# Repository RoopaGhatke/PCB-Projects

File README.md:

This repository showcases a collection of PCB design projects created using Altium Designer and KiCad. 
Each project involves complete development from schematic design to PCB layout and 3D model visualization.
These designs were developed from scratch as part of my self-learning journey, following well-structured tutorials to understand and apply industry-standard design principles. 
These projects not only helped me gain hands-on experience with PCB design tools and workflows, but also deepened my understanding of hardware design concepts, electrical best practices and design-for-manufacturing (DFM) techniques.

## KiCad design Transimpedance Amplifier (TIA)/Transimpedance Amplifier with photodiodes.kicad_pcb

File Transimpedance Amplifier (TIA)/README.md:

Transimpedance Amplifier with Photodiodes – Circuit Design Lab

This repository documents the week-long Circuit Design Laboratory course project where I designed, simulated, fabricated, and tested a Transimpedance Amplifier (TIA) using photodiodes. 
The work involved both hardware and simulation aspects using KiCad and PCB prototyping tools.

Project Overview
The goal was to design a transimpedance amplifier circuit to convert photocurrent from a photodiode into a measurable voltage. 
The project was carried out step by step — from schematic design to simulation, PCB layout, fabrication, soldering and final testing.

Tools Used
KiCad for schematic design, simulation (DC, AC, and transient), and PCB layout
PCB etching tools for single and double-layer board fabrication
Basic electronics lab tools for assembly and testing (multimeter, soldering iron, etc.)

Key Design Highlights

1. Circuit Type: Transimpedance amplifier using photodiodes
2. Simulation:
   DC Analysis: Verified operating point and biasing
   AC Analysis: Observed frequency response and gain-bandwidth
   Transient Analysis: Verified dynamic behavior to input signal changes
3. PCB Layouts:
   Designed both single-layer and double-layer PCBs
   Included placement of photodiodes, op-amp, feedback resistor and capacitor, power supply pins, and headers

Fabrication & Testing Insights

1. Double-Layer PCB Issues:
   Over-etching due to prolonged etching bath exposure
   Heat damage during soldering caused pin header sinking
   Via placement too close to traces led to short circuits

2. Single-Layer PCB Success:
   Proper etching and trace definition
   Stable soldering and component mounting
   Functional test successful with clean output response

Visual Documentation
Images are available in the /images directory:
Double-layer board (defective): shorted vias, over-etching
Single-layer board (working): clean layout, successful testing

Learnings
Hands-on experience with full PCB design cycle
Impact of layout decisions on board performance
Importance of thermal control during soldering
Troubleshooting real-world fabrication errors
Value of simulation in verifying design before manufacturing

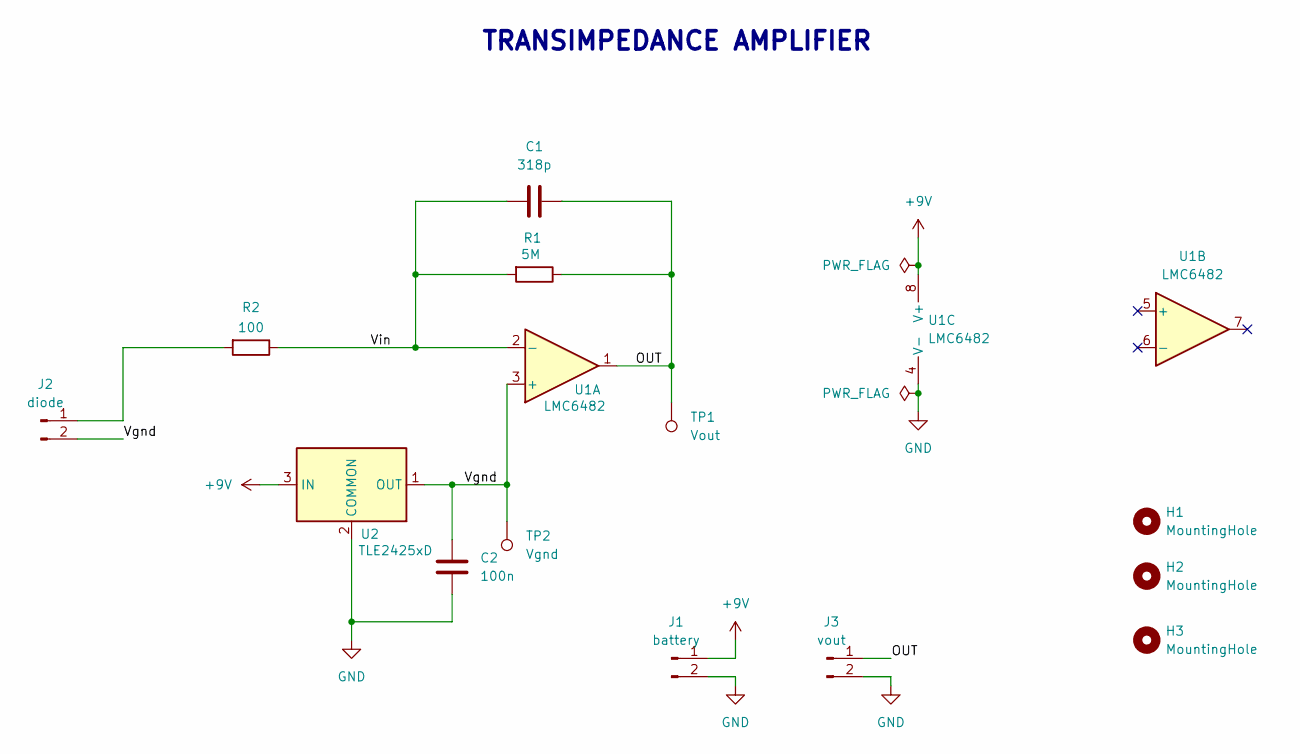
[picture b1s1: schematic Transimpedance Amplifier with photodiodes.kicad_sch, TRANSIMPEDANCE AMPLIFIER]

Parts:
C1: 318p; C_0805_2012Metric
C2: 100n; C_0805_2012Metric
H1, H2, H3: MountingHole; MountingHole_2.5mm_Pad
J1: battery; PinSocket_1x02_P2.54mm_Vertical
J2: diode; PinHeader_1x02_P2.54mm_Vertical
J3: vout; PinHeader_1x02_P2.54mm_Vertical
R1: 5M; R_0603_1608Metric
R2: 100; R_0603_1608Metric
TP1: Vout; TestPoint_Pad_1.0x1.0mm
TP2: Vgnd; TestPoint_Pad_1.0x1.0mm
U1: LMC6482; SOIC127P599X175-8N
U2: TLE2425xD; SOIC127P599X175-8N

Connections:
+9V: J1.1, U1.8 (V+), U2.3 (IN)
/OUT: C1.2, J3.1, R1.1, TP1.1, U1.1
/Vgnd: C2.1, J2.2, TP2.1, U1.3 (+), U2.1 (OUT)
/Vin: C1.1, R1.2, R2.1, U1.2 (-)
GND: C2.2, J1.2, J3.2, U1.4 (V-), U2.2 (COMMON)
unnamed: J2.1, R2.2

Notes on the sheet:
TRANSIMPEDANCE AMPLIFIER

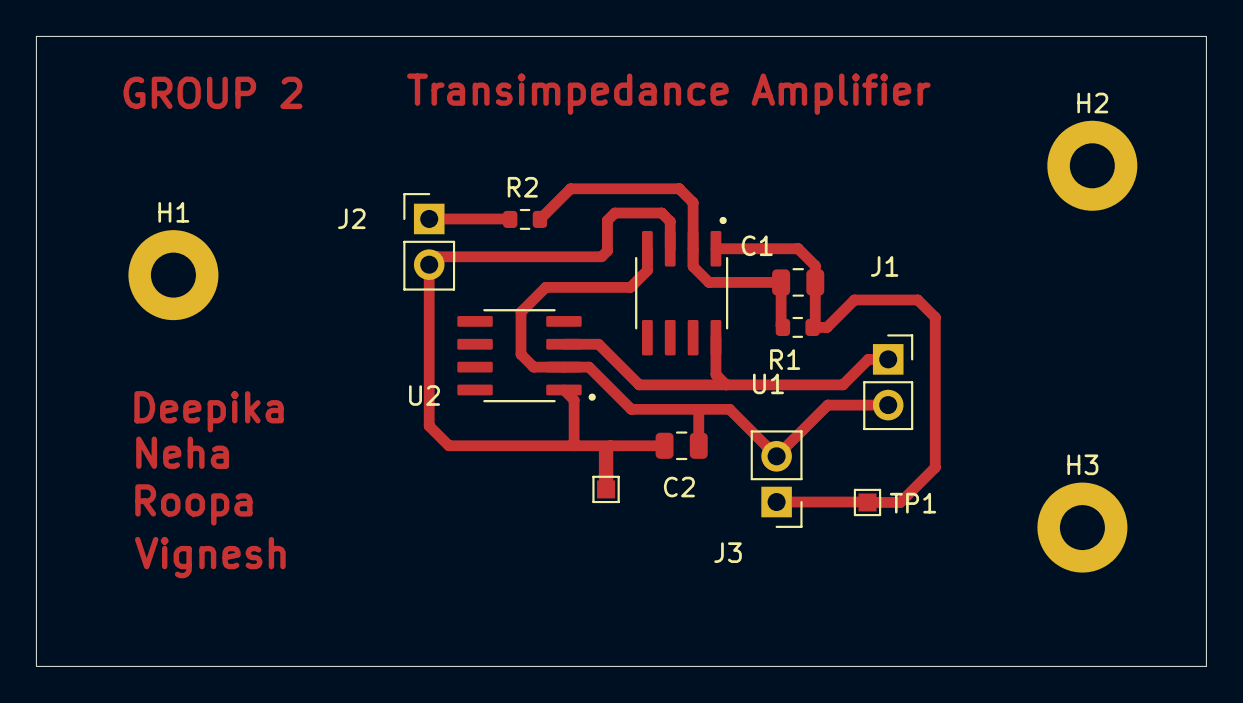
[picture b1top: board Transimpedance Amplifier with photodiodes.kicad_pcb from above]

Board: 2 copper layers, 65.0 x 35.0 mm, 14 parts (0 on the bottom side), 6 nets.

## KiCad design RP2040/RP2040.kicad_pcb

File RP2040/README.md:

This repository showcases a custom-designed RP2040-based development board, featuring both schematic and PCB layout files created using KiCad.
While the conceptual design was inspired by general community examples and official documentation, all schematic drawing and PCB layout work were done independently to reinforce hands-on learning.

Overview
This project revolves around the RP2040 microcontroller, a dual-core ARM Cortex-M0+ chip developed by Raspberry Pi.
The board includes all the essential components required for flashing, debugging and GPIO testing, making it ideal for embedded systems experimentation.

Features
1. USB Micro-B connector for power and programming
2. 3.3V LDO Voltage Regulator for clean power supply
3. External 12 MHz Crystal Oscillator for clock stability
4. 16MB QSPI Flash memory for storing firmware
5. Full GPIO access via dual-row headers

Design Details
Schematic: Created independently by referencing RP2040 datasheets and design guidelines
PCB Layout: Fully original – includes manual component placement, DRC checks and optimized 2-layer routing
Tool Used: KiCad (v9.0.3)

Files Included
Schematic - KiCad .sch files
PCB - KiCad .kicad_pcb layout files
Images - 3D board view, pcb layout

The board was designed as a 2-layer PCB, focusing on compact layout, proper signal routing and practical hardware bring-up considerations.
It was developed from scratch in KiCad as part of a personal learning exercise in microcontroller board design and embedded hardware prototyping.

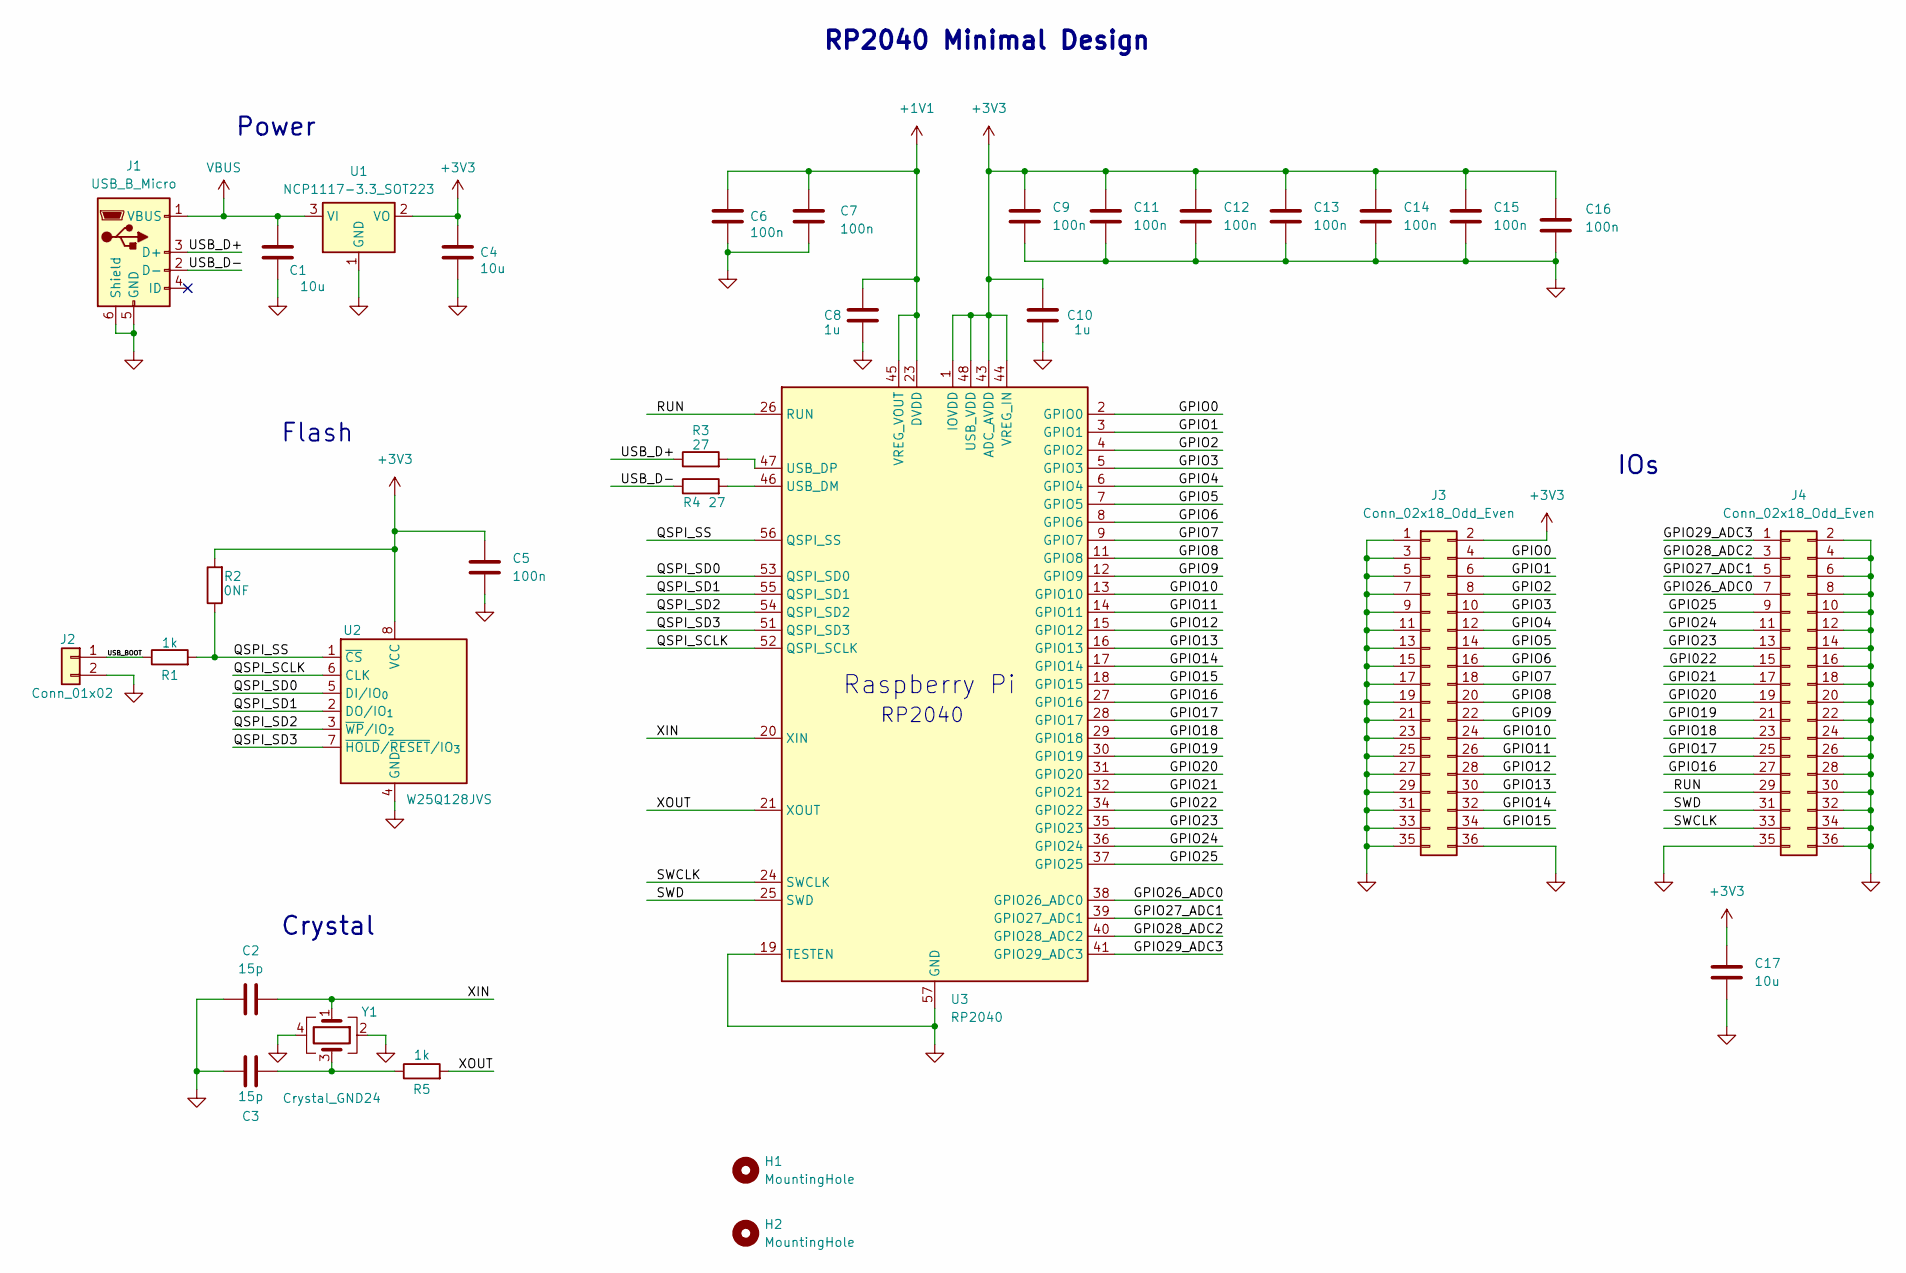
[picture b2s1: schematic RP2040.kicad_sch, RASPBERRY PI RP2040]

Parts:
C1, C4, C17: 10u; C_0201_0603Metric
C2, C3: 15p; C_0201_0603Metric
C5, C6, C7, C9, C11, C12, C13, C14, C15, C16: 100n; C_0201_0603Metric
C8, C10: 1u; C_0201_0603Metric
H1, H2: MountingHole; MountingHole_2.5mm
J1: USB_B_Micro; USB_Micro-B_Amphenol_10103594-0001LF_Horizontal
J2: Conn_01x02; PinHeader_1x02_P2.54mm_Vertical
J3, J4: Conn_02x18_Odd_Even; PinHeader_2x18_P2.54mm_Vertical_SMD
R1, R5: 1k; R_0201_0603Metric
R2: 0NF; R_0201_0603Metric
R3, R4: 27; R_0201_0603Metric
U1: NCP1117-3.3_SOT223; SOT-223-3_TabPin2
U2: W25Q128JVS; SOIC-8_5.3x5.3mm_P1.27mm
U3: RP2040; QFN-56-1EP_7x7mm_P0.4mm_EP3.2x3.2mm
Y1: Crystal_GND24; Crystal_SMD_Abracon_ABM8G-4Pin_3.2x2.5mm

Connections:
+1V1: C6.1, C7.1, C8.2, U3.23 (DVDD), U3.45 (VREG_VOUT), U3.50 (DVDD)
+3V3: C4.1, C5.1, C9.2, C10.2, C11.2, C12.2, C13.2, C14.2, C15.2, C16.2, C17.2, J3.2, R2.2, U1.2 (VO), U2.8 (VCC), U3.1 (IOVDD), U3.10 (IOVDD), U3.22 (IOVDD), U3.33 (IOVDD), U3.42 (IOVDD), U3.43 (ADC_AVDD), U3.44 (VREG_IN), U3.48 (USB_VDD), U3.49 (IOVDD)
/GPI022: J4.15, U3.34 (GPIO22)
/GPIO0: J3.4, U3.2 (GPIO0)
/GPIO1: J3.6, U3.3 (GPIO1)
/GPIO2: J3.8, U3.4 (GPIO2)
/GPIO3: J3.10, U3.5 (GPIO3)
/GPIO4: J3.12, U3.6 (GPIO4)
/GPIO5: J3.14, U3.7 (GPIO5)
/GPIO6: J3.16, U3.8 (GPIO6)
/GPIO7: J3.18, U3.9 (GPIO7)
/GPIO8: J3.20, U3.11 (GPIO8)
/GPIO9: J3.22, U3.12 (GPIO9)
/GPIO10: J3.24, U3.13 (GPIO10)
/GPIO11: J3.26, U3.14 (GPIO11)
/GPIO12: J3.28, U3.15 (GPIO12)
/GPIO13: J3.30, U3.16 (GPIO13)
/GPIO14: J3.32, U3.17 (GPIO14)
/GPIO15: J3.34, U3.18 (GPIO15)
/GPIO16: J4.27, U3.27 (GPIO16)
/GPIO17: J4.25, U3.28 (GPIO17)
/GPIO18: J4.23, U3.29 (GPIO18)
/GPIO19: J4.21, U3.30 (GPIO19)
/GPIO20: J4.19, U3.31 (GPIO20)
/GPIO21: J4.17, U3.32 (GPIO21)
/GPIO23: J4.13, U3.35 (GPIO23)
/GPIO24: J4.11, U3.36 (GPIO24)
/GPIO25: J4.9, U3.37 (GPIO25)
/GPIO26_ADC0: J4.7, U3.38 (GPIO26_ADC0)
/GPIO27_ADC1: J4.5, U3.39 (GPIO27_ADC1)
/GPIO28_ADC2: J4.3, U3.40 (GPIO28_ADC2)
/GPIO29_ADC3: J4.1, U3.41 (GPIO29_ADC3)
/QSPI_SCLK: U2.6 (CLK), U3.52 (QSPI_SCLK)
/QSPI_SD0: U2.5 (DI/IO_{0}), U3.53 (QSPI_SD0)
/QSPI_SD1: U2.2 (DO/IO_{1}), U3.55 (QSPI_SD1)
/QSPI_SD2: U2.3 (~WP/IO_{2}), U3.54 (QSPI_SD2)
/QSPI_SD3: U2.7 (~HOLD/~RESET/IO_{3}), U3.51 (QSPI_SD3)
/QSPI_SS: R1.2, R2.1, U2.1 (~CS), U3.56 (QSPI_SS)
/RUN: J4.29, U3.26 (RUN)
/SWCLK: J4.33, U3.24 (SWCLK)
/SWD: J4.31, U3.25 (SWD)
/USB_BOOT: J2.1, R1.1
/USB_D+: J1.3 (D+), R3.1
/USB_D-: J1.2 (D-), R4.1
/XIN: C2.2, U3.20 (XIN), Y1.1
/XOUT: R5.2, U3.21 (XOUT)
GND: C1.2, C2.1, C3.1, C4.2, C5.2, C6.2, C7.2, C8.1, C9.1, C10.1, C11.1, C12.1, C13.1, C14.1, C15.1, C16.1, C17.1, J1.5 (GND), J1.6 (Shield), J2.2, J3.1, J3.3, J3.5, J3.7, J3.9, J3.11, J3.13, J3.15, J3.17, J3.19, J3.21, J3.23, J3.25, J3.27, J3.29, J3.31, J3.33, J3.35, J3.36, J4.2, J4.4, J4.6, J4.8, J4.10, J4.12, J4.14, J4.16, J4.18, J4.20, J4.22, J4.24, J4.26, J4.28, J4.30, J4.32, J4.34, J4.35, J4.36, U1.1 (GND), U2.4 (GND), U3.19 (TESTEN), U3.57 (GND), Y1.2, Y1.4
unnamed: C3.2, R5.1, Y1.3
unnamed: R4.2, U3.46 (USB_DM)
unnamed: R3.2, U3.47 (USB_DP)
VBUS: C1.1, J1.1 (VBUS), U1.3 (VI)

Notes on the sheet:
IOs
Raspberry Pi
Flash
Power
Crystal
RP2040 Minimal Design
RP2040

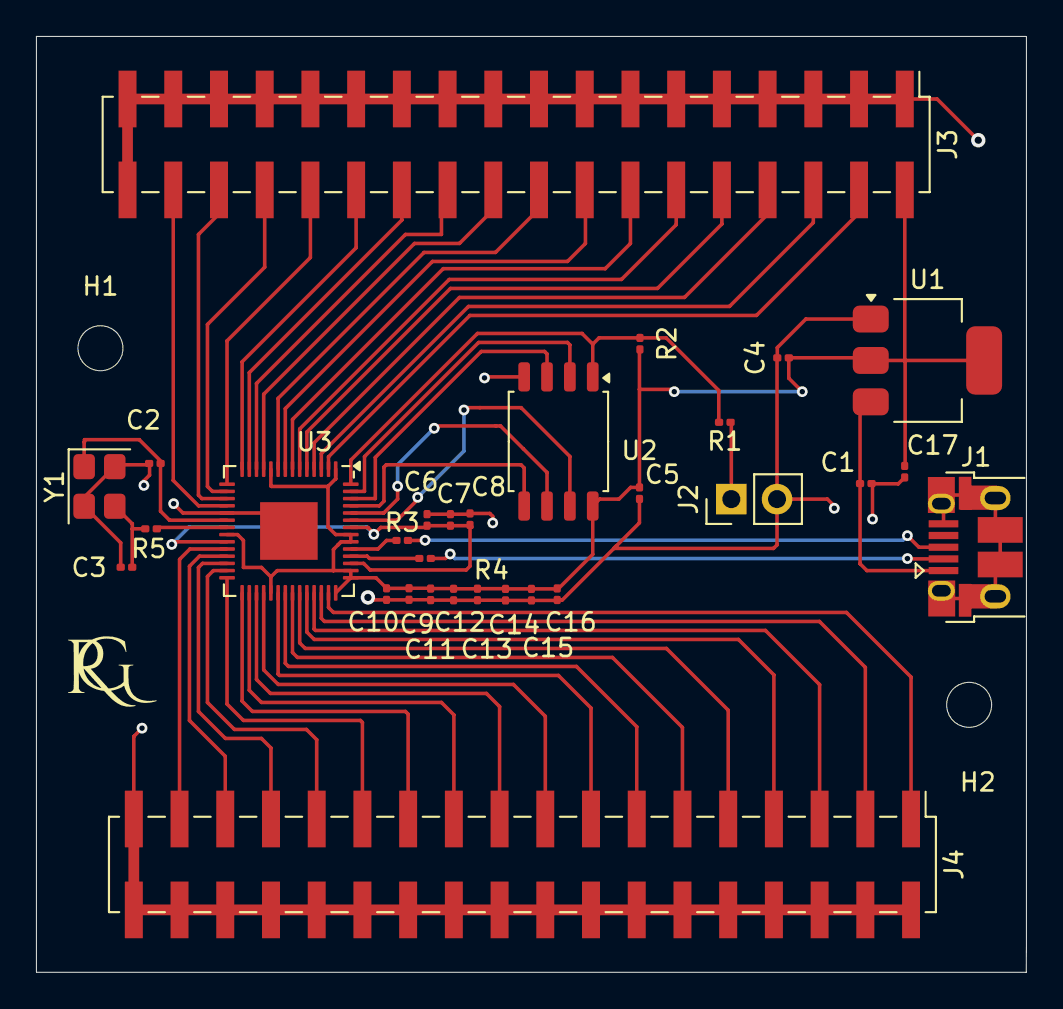
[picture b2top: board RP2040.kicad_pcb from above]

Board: 2 copper layers, 55.0 x 52.0 mm, 32 parts (0 on the bottom side), 51 nets.

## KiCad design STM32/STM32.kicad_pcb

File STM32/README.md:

This repository showcases a custom-designed STM32-based development board, featuring both schematic and PCB layout files created using KiCad. 
While the conceptual design was inspired by an online tutorial by Phil’s Lab, all schematic drawing and PCB layout work were done independently to reinforce hands-on learning.

Overview
This project revolves around the STM32F103C8T6 microcontroller, a widely-used ARM Cortex-M3 chip that serves as an excellent entry point for embedded systems and bare-metal firmware development.
The board provides all the basic peripherals required to begin STM32 experimentation, flashing and GPIO testing.

Features
1. SWD (Serial Wire Debug) Header for programming and in-circuit debugging
2. 3.3V Voltage Regulator for clean power supply
3. Reset Button to manually restart the MCU
4. User Button connected to GPIO for input testing
5. Status LED for simple visual output
6. 16 MHz Crystal Oscillator with load capacitors for clock stability

Design Details
Schematic: Created independently by referencing the block design principles shown in Phil’s Lab tutorial.
PCB Layout: Fully original – includes custom component placement, net class setup, design rule checking and optimized 2-layer routing.
Tool Used: KiCad (v9)

Files Included
Schematic             # KiCad .sch files
PCB                   # .kicad_pcb layout files
BOM                   # Bill of Materials
Image                 # 3D previews

The board was designed as a 2-layer PCB, focusing on compact layout, proper signal routing, and practical hardware bring-up considerations. 
It was developed from scratch in KiCad as part of a personal learning exercise in microcontroller board design and hardware prototyping.

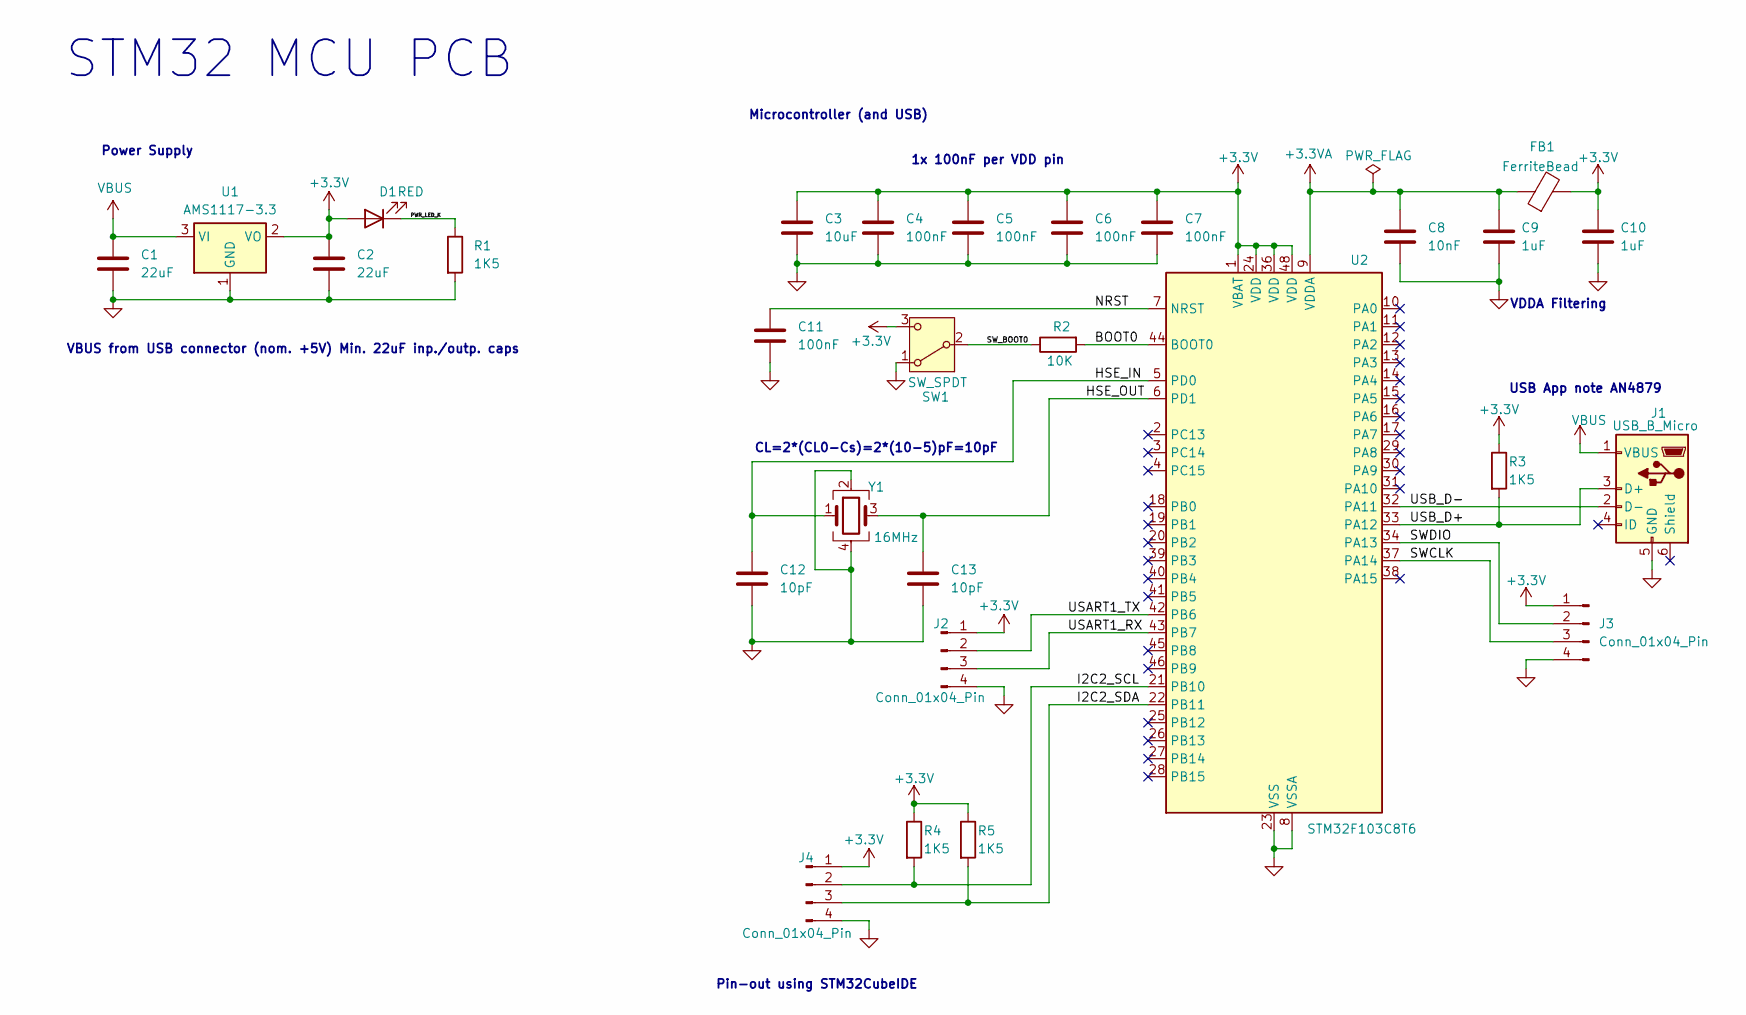
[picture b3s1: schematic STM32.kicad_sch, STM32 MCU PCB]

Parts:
C1, C2: 22uF; C_0805_2012Metric
C3: 10uF; C_0603_1608Metric
C4, C5, C6, C7, C11: 100nF; C_0402_1005Metric
C8: 10nF; C_0603_1608Metric
C9, C10: 1uF; C_0402_1005Metric
C12, C13: 10pF; C_0402_1005Metric
D1: RED; LED_0603_1608Metric
FB1: FerriteBead; L_0603_1608Metric
J1: USB_B_Micro; USB_Micro-B_Wuerth_629105150521
J2, J3, J4: Conn_01x04_Pin; PinHeader_1x04_P2.54mm_Vertical
R1, R3, R4, R5: 1K5; R_0402_1005Metric
R2: 10K; R_0402_1005Metric
SW1: SW_SPDT; SW_SPDT_PCM12
U1: AMS1117-3.3; SOT-223-3_TabPin2
U2: STM32F103C8T6; LQFP-48_7x7mm_P0.5mm
Y1: 16MHz; Crystal_SMD_3225-4Pin_3.2x2.5mm

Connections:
+3.3V: C2.1, C3.1, C4.1, C5.1, C6.1, C7.1, C10.1, D1.2 (A), FB1.2, J2.1, J3.1, J4.1, R3.1, R4.1, R5.1, SW1.3 (C), U1.2 (VO), U2.1 (VBAT), U2.24 (VDD), U2.36 (VDD), U2.48 (VDD)
+3.3VA: C8.1, C9.1, FB1.1, U2.9 (VDDA)
/BOOT0: R2.2, U2.44 (BOOT0)
/HSE_IN: C12.1, U2.5 (PD0), Y1.1
/HSE_OUT: C13.1, U2.6 (PD1), Y1.3
/I2C2_SCL: J4.2, R4.2, U2.21 (PB10)
/I2C2_SDA: J4.3, R5.2, U2.22 (PB11)
/NRST: C11.1, U2.7 (NRST)
/PWR_LED_K: D1.1 (K), R1.1
/SWCLK: J3.3, U2.37 (PA14)
/SWDIO: J3.2, U2.34 (PA13)
/SW_BOOT0: R2.1, SW1.2 (B)
/USART1_RX: J2.3, U2.43 (PB7)
/USART1_TX: J2.2, U2.42 (PB6)
/USB_D+: J1.3 (D+), R3.2, U2.33 (PA12)
/USB_D-: J1.2 (D-), U2.32 (PA11)
GND: C1.2, C2.2, C3.2, C4.2, C5.2, C6.2, C7.2, C8.2, C9.2, C10.2, C11.2, C12.2, C13.2, J1.5 (GND), J2.4, J3.4, J4.4, R1.2, SW1.1 (A), U1.1 (GND), U2.8 (VSSA), U2.23 (VSS), U2.35 (VSS), U2.47 (VSS), Y1.2, Y1.4
VBUS: C1.1, J1.1 (VBUS), U1.3 (VI)

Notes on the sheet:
STM32 MCU PCB
Power Supply
CL=2*(CL0-Cs)=2*(10-5)pF=10pF
Microcontroller (and USB)
Pin-out using STM32CubeIDE
VBUS from USB connector (nom. +5V) Min. 22uF inp./outp. caps
USB App note AN4879
VDDA Filtering
1x 100nF per VDD pin

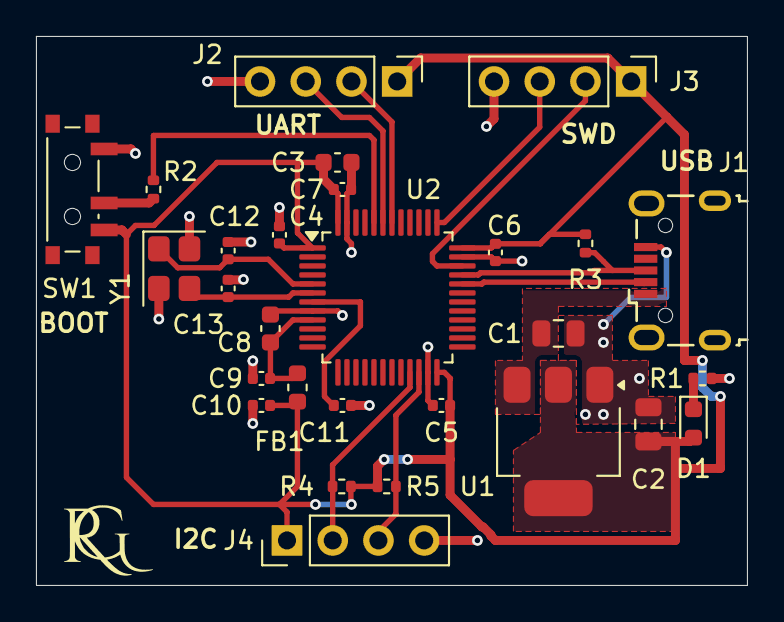
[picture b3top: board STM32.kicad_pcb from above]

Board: 2 copper layers, 39.5 x 30.5 mm, 28 parts (0 on the bottom side), 18 nets.

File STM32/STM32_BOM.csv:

"Id";"Designator";"Footprint";"Quantity";"Designation";"Supplier and ref";
1;"R4,R5,R1,R3";"R_0402_1005Metric";4;"1K5";;;
2;"SW1";"SW_SPDT_PCM12";1;"SW_SPDT";;;
3;"C9,C10";"C_0402_1005Metric";2;"1uF";;;
4;"J3,J4,J2";"PinHeader_1x04_P2.54mm_Vertical";3;"Conn_01x04_Pin";;;
5;"D1";"LED_0603_1608Metric";1;"RED";;;
6;"FB1";"L_0603_1608Metric";1;"FerriteBead";;;
7;"C6,C11,C4,C7,C5";"C_0402_1005Metric";5;"100nF";;;
8;"Y1";"Crystal_SMD_3225-4Pin_3.2x2.5mm";1;"16MHz";;;
9;"R2";"R_0402_1005Metric";1;"10K";;;
10;"C13,C12";"C_0402_1005Metric";2;"10pF";;;
11;"U1";"SOT-223-3_TabPin2";1;"AMS1117-3.3";;;
12;"C1,C2";"C_0805_2012Metric";2;"22uF";;;
13;"C3";"C_0603_1608Metric";1;"10uF";;;
14;"C8";"C_0603_1608Metric";1;"10nF";;;
15;"U2";"LQFP-48_7x7mm_P0.5mm";1;"STM32F103C8T6";;;
16;"J1";"USB_Micro-B_Wuerth_629105150521";1;"USB_B_Micro";;;
